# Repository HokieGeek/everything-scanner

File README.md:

# Olive's Scanner 

Toy I am making my toddler so that when she touches an object the "scanner" vibrates and lights up. Should second as a flashlight, of sorts.

### Prototype

[Album](http://imgur.com/a/BFDh3)

## Design

## Parts list

* [ATtiny13A](http://www.atmel.com/images/doc8126.pdf) - The driver of the whole thing
* [MCP23S08](http://www.mouser.com/ds/2/268/21919b-65915.pdf) - SPI 8-bit I/O expander used to drive just the LEDs
* [SparkFun's LED Rainbow Pack](https://www.sparkfun.com/products/13767) - Got it in a recent order for free as a christmas giveaway
* [Vibrator motor from an old phone]() - Took it out of my waterlogged MotoX :-D
* [CdS Photocell](http://cdn.sparkfun.com/datasheets/Sensors/LightImaging/SEN-09088.pdf) - When she touches this sensor to an object, the LEDs and motor activate

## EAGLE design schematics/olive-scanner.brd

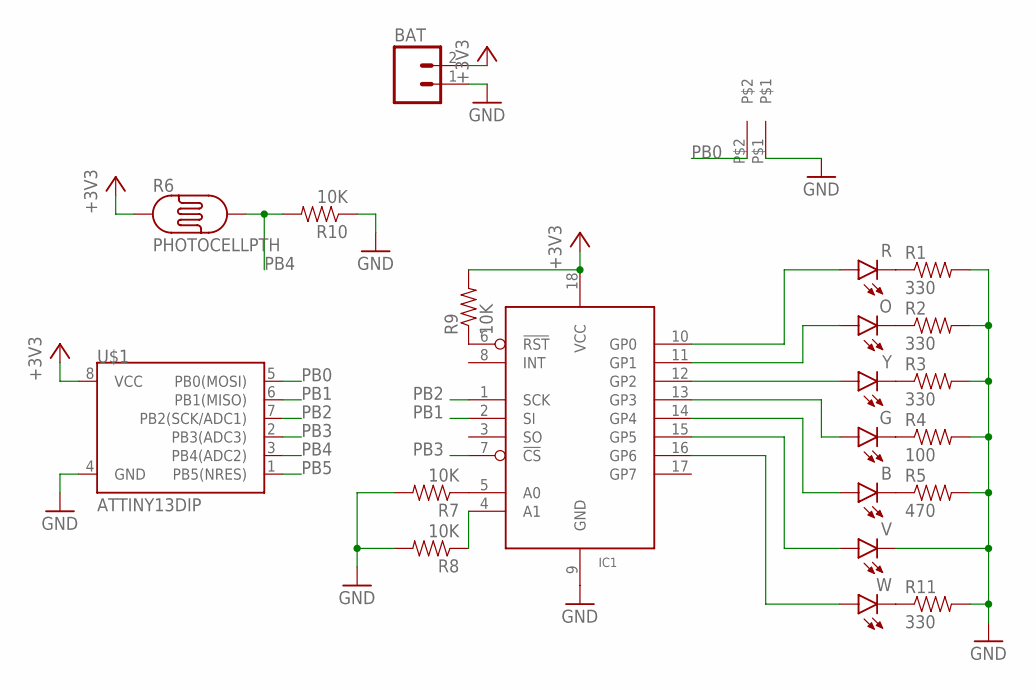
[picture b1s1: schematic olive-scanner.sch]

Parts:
B: LED5MM
BAT: M02LOCK; 1X02_LOCK
G: LED5MM
IC1: MCP23S08/P; DIL18
O: LED5MM
R: LED5MM
R1, R2, R3, R11: 330; AXIAL-0.3
R4: 100; AXIAL-0.3
R5: 470; AXIAL-0.3
R6: PHOTOCELLPTH; PHOTOCELL
R7, R8, R9, R10: 10K; AXIAL-0.3
U$1: ATTINY13DIP; DIP08
U$2: PHONE_VIBRATOR
V: LED5MM
W: LED5MM
Y: LED5MM

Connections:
+3V3: BAT.2, IC1.18 (VCC), R6.1, R9.P$2 (2), U$1.8 (VCC)
GND: BAT.1, IC1.9 (GND), R1.P$2 (2), R2.P$2 (2), R3.P$2 (2), R4.P$2 (2), R5.P$2 (2), R7.P$2 (2), R8.P$2 (2), R10.P$1 (1), R11.P$2 (2), U$1.4 (GND), U$2.P$1, V.K (C)
unnamed: IC1.4 (A1), R8.P$1 (1)
unnamed: IC1.6 (!RST), R9.P$1 (1)
unnamed: IC1.5 (A0), R7.P$1 (1)
unnamed: R.K (C), R1.P$1 (1)
unnamed: O.K (C), R2.P$1 (1)
unnamed: R3.P$1 (1), Y.K (C)
unnamed: G.K (C), R4.P$1 (1)
unnamed: B.K (C), R5.P$1 (1)
unnamed: R11.P$1 (1), W.K (C)
unnamed: IC1.16 (GP6), W.A
unnamed: IC1.10 (GP0), R.A
unnamed: IC1.11 (GP1), O.A
unnamed: IC1.12 (GP2), Y.A
unnamed: G.A, IC1.13 (GP3)
unnamed: B.A, IC1.14 (GP4)
unnamed: IC1.15 (GP5), V.A
PB0: U$1.5 (PB0(MOSI)), U$2.P$2
PB1: IC1.2 (SI), U$1.6 (PB1(MISO))
PB2: IC1.1 (SCK), U$1.7 (PB2(SCK/ADC1))
PB3: IC1.7 (!CS), U$1.2 (PB3(ADC3))
PB4: R6.2, R10.P$2 (2), U$1.3 (PB4(ADC2))
PB5: U$1.1 (PB5(NRES))

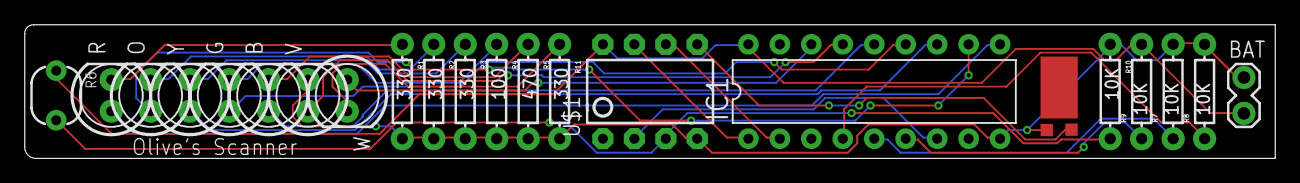
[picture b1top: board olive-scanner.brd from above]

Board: 2 copper layers, 101.0 x 10.8 mm, 22 parts (0 on the bottom side), 23 nets.

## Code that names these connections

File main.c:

// #define F_CPU 9600000UL

#include <avr/interrupt.h>
#include <avr/sleep.h>
#include <util/delay.h>

#include "mcp23x08.h"

#define FALSE 0
#define TRUE !(FALSE)

#define VIBRATOR_PIN PB0
#define VIBRATE_PULSE 255

#define LEDS_PIN_DATA PB1
#define LEDS_PIN_SERIALCLOCK PB2
#define LEDS_PIN_CHIPSELECT PB3
#define MCP23X08_SLAVE_ADDRESS_A0 0
#define MCP23X08_SLAVE_ADDRESS_A1 0
#define NUM_LEDS 6
#define NUM_LED_PATTERNS 4
#define ANIMATION_REPETITION 5

#define PHOTOCELL_PIN PB4
#define PHOTOCELL_ACTIVATE_THRESHOLD 330 // TODO: make this a diff from ambient?

uint8_t isAnimating = FALSE;
uint16_t currentAmbient = 800;
mcp23s08Device mcp23s08;

inline void ledsWrite(uint8_t leds) {
    MCP23S08_GpioWrite(&mcp23s08, leds);
}

void ledPattern_Alternating(void) {
    ledsWrite(0b01101010);
    _delay_ms(500);
    ledsWrite(0b01010101);
    _delay_ms(500);
}

void ledPattern_KITT(void) {
    int i = 0;
    for (; i < NUM_LEDS; i++) {
        ledsWrite(((1 << i)|(1 << NUM_LEDS)));
        _delay_ms(100);
    }
    i -= 2;
    for (; i >= 0; i--) {
        ledsWrite(((1 << i)|(1 << NUM_LEDS)));
        _delay_ms(100);
    }
}

void ledPattern_LandingStrip(void) {
    uint8_t pattern = 0;
    for (uint8_t i = 0; i < NUM_LEDS; i++) {
        pattern |= (1 << i);
        ledsWrite((pattern|(1 << NUM_LEDS)));
        _delay_ms(150);
    }
    ledsWrite(0b01000000);
    _delay_ms(150);
}

void ledPattern_Blinky(void) {
    ledsWrite(0b01111111);
    _delay_ms(500);
    ledsWrite(0b01000000);
    _delay_ms(500);
}

uint16_t readPhotocell(void) {
    uint16_t photocellVal = 0;
    for (uint8_t i = 0; i < 8; i++) {
        ADCSRA |= (1 << ADSC); // Start the conversion

        while (ADCSRA & (1 << ADSC)); // Wait for conversion

        photocellVal += ADC;
    }

    return (uint16_t)(photocellVal / 8);
}

void animateLeds(void) {
    uint16_t rand = readPhotocell() % (NUM_LED_PATTERNS-1);
    isAnimating = TRUE;
    for (uint8_t i = 0; i < ANIMATION_REPETITION && isAnimating; i++) {
        switch (rand) {
        case 0: ledPattern_Alternating(); break;
        case 1: ledPattern_KITT(); break;
        case 2: ledPattern_LandingStrip(); break;
        case 3: ledPattern_Blinky(); break;
        default: break;
        }
    }
}

inline void vibrate(uint16_t pulse) {
    OCR0A = pulse;
    _delay_ms(500);
    OCR0A = 0x00;
}

inline int isTouching(void) {
    // TODO: better way to determine this?
    if (readPhotocell() < PHOTOCELL_ACTIVATE_THRESHOLD) {
        return TRUE;
    } else {
        return FALSE;
    }
}

void analyze_and_activate(void) {
    if (isTouching()) {
        // if (isAnimating) {
        //     isAnimating = FALSE;
        // }
        vibrate(VIBRATE_PULSE);
        animateLeds();
    } else { // Turn off all LEDs
        // isAnimating = FALSE;
        ledsWrite(0x00);
    }
}

ISR(WDT_vect) {
    ADCSRA |= (1 << ADEN);  // Enable ADC
    analyze_and_activate();
    ADCSRA &= ~(1 << ADEN);  // Disable ADC
}

inline void init_pins(void) {
    // Vibrator
    TCCR0B |= (1 << CS01); // clock/8 (See 11-9)
    TCCR0A |= (1 << WGM01) | (1 << WGM00); // Set for fast PWM with 0xFF Max (See 11-8)
    TCCR0A |= (1 << COM0A1); // Clear on compare match (See 11-5)

    DDRB |= (1 << VIBRATOR_PIN);

    // LEDS
    mcp23s08.spi.chipSelect = LEDS_PIN_CHIPSELECT;
    mcp23s08.spi.serialClock = LEDS_PIN_SERIALCLOCK;
    mcp23s08.spi.serialDataInput = LEDS_PIN_DATA;

    MCP23S08_Init(MCP23X08_SLAVE_ADDRESS_A0, MCP23X08_SLAVE_ADDRESS_A1, &mcp23s08);
    MCP23S08_IodirWrite(&mcp23s08, 0x00); // Set all pins as output pins
    ledsWrite(0x00); // Start them off

    // The photocell ADC. Enable ADC2 / PB4 as an ADC pin
    ADMUX |= (0 << REFS0) | (1 << MUX1) | (0 << MUX0);
    ADCSRA |= (1 << ADPS1) | (1 << ADPS0) | (1 << ADEN); // Enable ADC and set prescaler to clock/128
}

inline void init_interrupts(void) {
    // See table 8-2 on datasheet
    WDTCR |= (1 << WDP2) | (1 << WDP0); // Sleep for ~30s
    // WDTCR |= (1 << WDP2); // Sleep for ~15s
    WDTCR |= (1 << WDTIE); // Enable watchdog timer

    sei();

    set_sleep_mode(SLEEP_MODE_PWR_DOWN);
}

int __attribute__((OS_main)) main(void) {
    init_pins();
    init_interrupts();

    ADCSRA &= ~(1 << ADEN);  // Disable ADC (to save power)

    currentAmbient = readPhotocell();

    for (;;) {
        sleep_mode();
    }

    return 0;
}

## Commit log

2015-11-17 Initial commit of something that actually works as intended!
2015-11-17 Trying to keep the hex size down
2015-11-17 I do not need this here
2015-11-17 Doing some very quick and simple tweaks which might reduce the size of the binary
2015-11-17 Adding yet another thing to attempt to reduce the size
2015-11-17 Fleshing out the readme
2015-11-18 Trying out some optimizations, hopefully
2015-11-18 Github should be smarter than this
2015-11-18 I knew it
2015-11-18 Reduced the binary size greatly. Now I have a whole 500 bytes to play with!
2015-11-18 Added targets for the fuses
2015-11-18 Schematics placeholder
2015-11-20 Adding some MCP23S08 related code
2015-11-20 Made the byte writing stuff smarterer
2015-11-20 Empty file
2015-11-20 Over-engineering this
    Probably going to put some of this in a location in avr-lib
2015-11-20 Adding Travis CI badge
2015-11-20 Fixing typo. Thanks, TravisCI!
2015-11-20 Using container-based config
2015-11-20 Adding a 'size' target because this matters, dang it!
2015-11-20 Adding check for the size of the binary
2015-11-20 Whoops
2015-11-21 Attempted to do some external stuff... We shall see
2015-11-21 Fixed the expander line
2015-11-21 Ignoring new Eagle lock files
2015-11-21 Adding schematics
2015-11-22 Modifying project file
2015-11-22 Made it smaterter
2015-11-23 Did the schematics and updated the docs
2015-11-23 Only doing an animation once the previous one ends
2015-11-23 Updated the prototype pic and the design images
2015-11-23 I clearly didn't compile this before committing
    Time for a git hook
2015-11-23 *sigh*
2015-11-23 Fixed a couple of typoish things
2015-11-23 ls was a poor size indicator. Looking at avr-size
2015-11-23 Refactoring to make use of the spi.h impl I have
2015-11-23 Using correct data type
2015-11-23 Decoupling from the mcp23s08
2015-11-24 Trying to put the mcp23x08 code in its own files and leverage my spi code, but SIZE!
2015-11-24 I don't think that I'm going to put the patterns in their own file
2015-11-24 Getting slightly better, but still...
2015-11-25 Got the binary size back down (good bye, malloc!) and still building with separate files
2015-11-25 I think I have a bug passing the spi device around...
2015-11-25 Maybe this will get travis-ci working?
2015-11-25 I think this approach is better
2015-11-25 Cleaning up this file a little
2015-11-25 Cleaning up this file and correcting Init3WireSpiDevice
2015-11-25 Cleaning up this file a little bit and maybe trigger Travis-CI?
2015-11-25 Whoops. Thought I had gotten them all
2015-11-25 Dang it
2015-11-25 Trying to start adding the patterns. Bet I broke some stuff!
2015-11-25 Hmm..
2015-11-25 Before I go home...
2015-11-26 w00t!
2015-11-26 Tested the first two patterns
2015-11-26 I don't think the random patterns thing will be happening
2015-11-27 Cleaned up a little bit
2015-11-27 Added animations and cleaned up a bit
2015-11-28 Getting closer, but running out of room!
2015-11-28 Randomly selecting the animations now. Only thing left is to better calibrate the sensor
2015-11-28 Removed unecessary makefile
2015-11-29 Well... Being more careful with my datatypes really paid off
2015-11-29 Whoops. Broked it
2015-11-29 Refactored SPI code to allow for more reuse later
2015-11-30 Removed extra spaces
2015-11-30 Now taking many samples for a reading
2015-11-30 Adding test sketch so that I can figure out the logic I need for the light sensor to behave as I want it to
2015-12-04 Adding WDT functionality to see how that affects things
2015-12-04 Adding ability to use Travis to test the test sketch
2015-12-04 Whatever

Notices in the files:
parts and their libraries:
SparkFun-LED: Licensing: Creative Commons ShareAlike 4.0 International - https://creativecommons.org/licenses/by-sa/4.0
